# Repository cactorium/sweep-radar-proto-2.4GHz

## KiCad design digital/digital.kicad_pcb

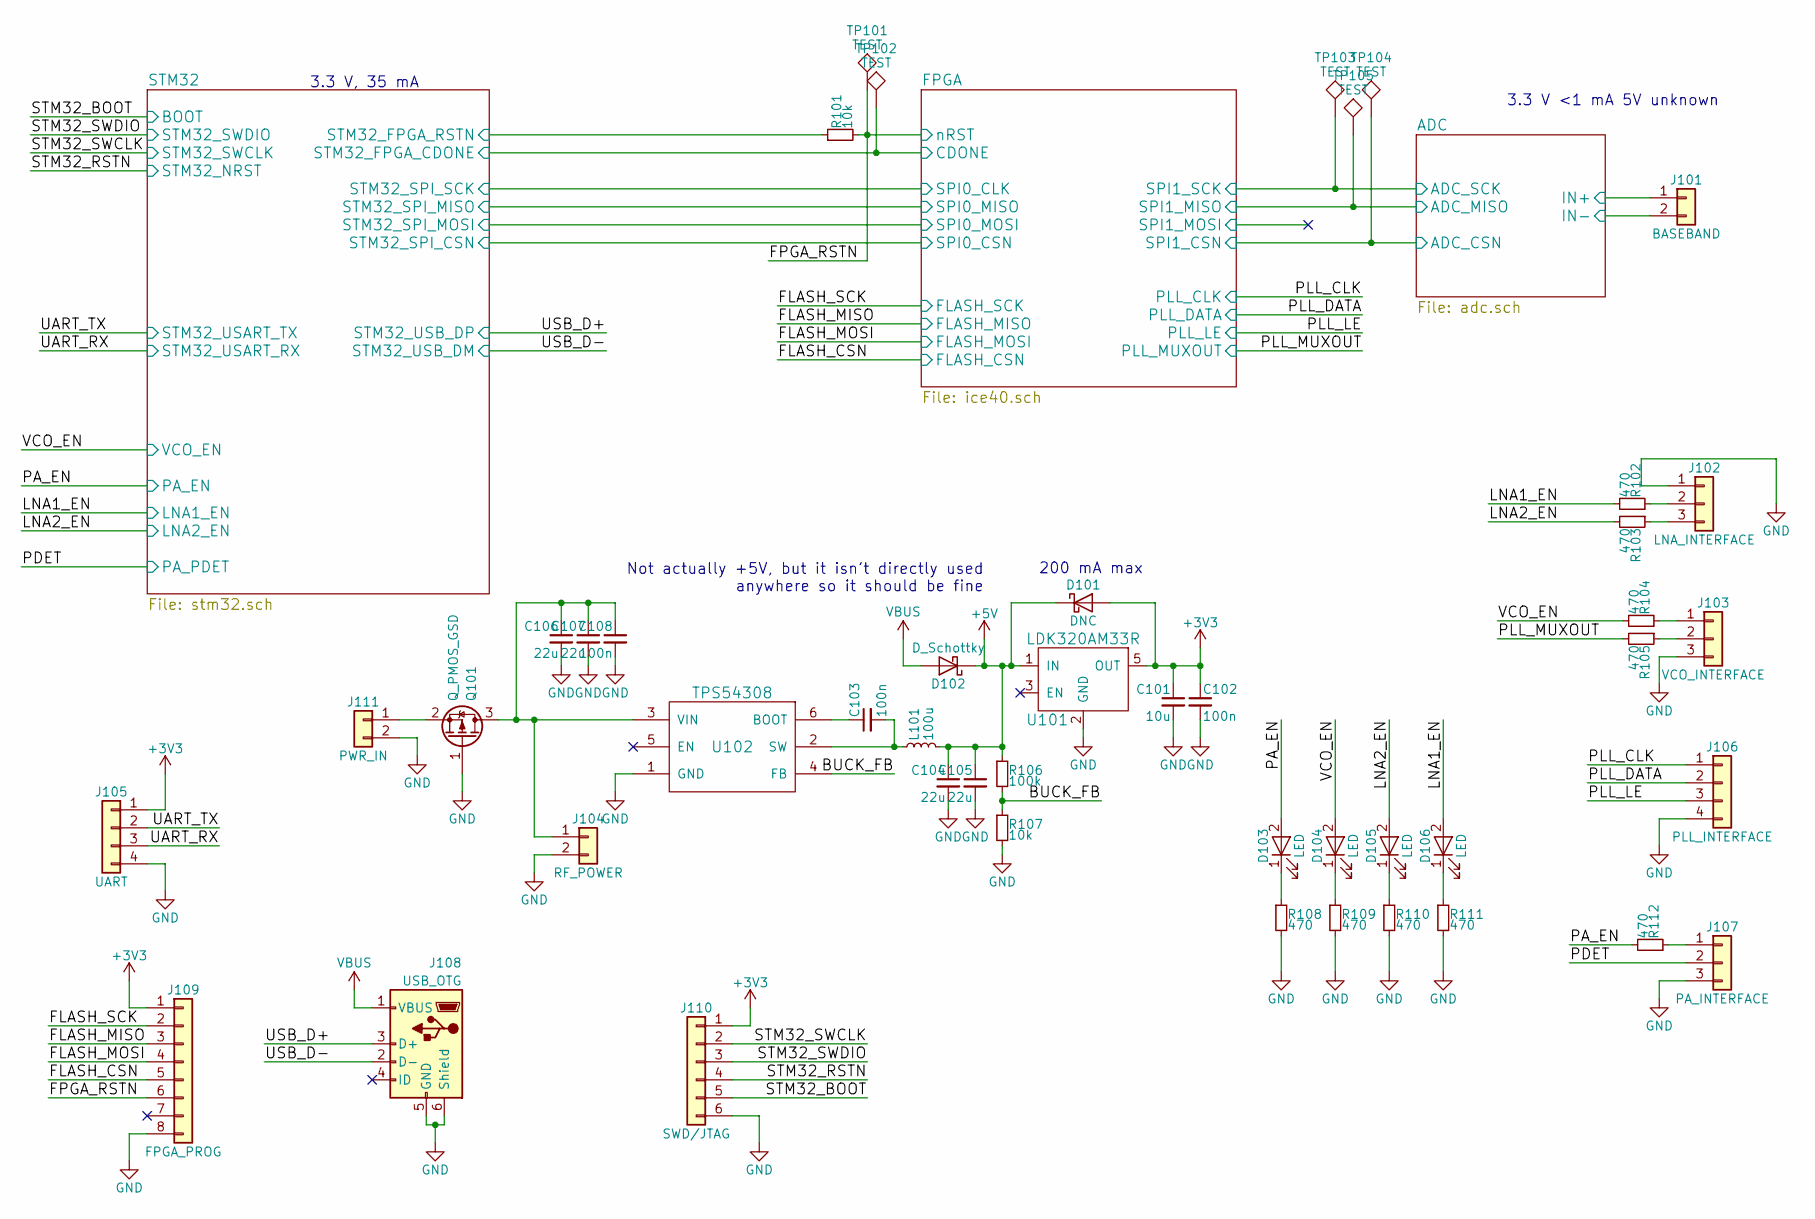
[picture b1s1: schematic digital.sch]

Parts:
C101: 10u; C_0805_HandSoldering
C102, C103, C108: 100n; C_0603_HandSoldering
C104, C105, C106, C107: 22u; C_1210_HandSoldering
D101: DNC; Panasonic_Diode-1006
D102: D_Schottky; Panasonic_Diode-1006
D103, D104, D105, D106: LED; D_0603
J101: BASEBAND; Pin_Header_Straight_1x02_Pitch2.54mm
J102: LNA_INTERFACE; Pin_Header_Straight_1x03_Pitch2.54mm
J103: VCO_INTERFACE; Pin_Header_Straight_1x03_Pitch2.54mm
J104: RF_POWER; Pin_Header_Straight_1x02_Pitch2.54mm
J105: UART; Pin_Header_Straight_2x02_Pitch2.54mm
J106: PLL_INTERFACE; Pin_Header_Straight_1x04_Pitch2.54mm
J107: PA_INTERFACE; Pin_Header_Straight_1x03_Pitch2.54mm
J108: USB_OTG; 10118194
J109: FPGA_PROG; Pin_Header_Straight_2x04_Pitch2.54mm
J110: SWD/JTAG; Pin_Header_Straight_2x03_Pitch2.54mm
J111: PWR_IN; Pin_Header_Straight_1x02_Pitch2.54mm
L101: 100u; Murata_DG6050C
Q101: Q_PMOS_GSD; SOT-23
R101, R107: 10k; R_0603_HandSoldering
R102, R103, R104, R105, R108, R109, R110, R111, R112: 470; R_0603_HandSoldering
R106: 100k; R_0402
TP101, TP102, TP103, TP104, TP105: TEST; 1Pin
U101: LDK320AM33R; ST_SOT23-5L
U102: TPS54308; TI-SOT-23-6

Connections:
+5V: C104.1, C105.1, D101.1 (K), D102.1 (K), L101.2, R106.1, U101.1 (IN); also elsewhere on the board
/ADC/ADC_CSN: TP104.1; also elsewhere on the board
/ADC/ADC_MISO: TP105.1; also elsewhere on the board
/ADC/ADC_SCK: TP103.1; also elsewhere on the board
/ADC/IN+: J101.1; also elsewhere on the board
/ADC/IN-: J101.2; also elsewhere on the board
/BUCK_FB: R106.2, R107.1, U102.4 (FB)
/FLASH_CSN: J109.3; also elsewhere on the board
/FLASH_MISO: J109.4; also elsewhere on the board
/FLASH_MOSI: J109.5; also elsewhere on the board
/FPGA/CDONE: TP102.1; also elsewhere on the board
/LNA1_EN: D106.2 (A), R102.2; also elsewhere on the board
/LNA2_EN: D105.2 (A), R103.2; also elsewhere on the board
/PA_EN: D103.2 (A), R112.2; also elsewhere on the board
/PDET: J107.2; also elsewhere on the board
/PLL_CLK: J106.1; also elsewhere on the board
/PLL_DATA: J106.2; also elsewhere on the board
/PLL_LE: J106.3; also elsewhere on the board
/PLL_MUXOUT: R105.2; also elsewhere on the board
/STM32/STM32_FPGA_RSTN: R101.1; also elsewhere on the board
/STM32_BOOT: J110.5; also elsewhere on the board
/STM32_RSTN: J110.4; also elsewhere on the board
/STM32_SWCLK: J110.2; also elsewhere on the board
/STM32_SWDIO: J110.3; also elsewhere on the board
/UART_RX: J105.3; also elsewhere on the board
/UART_TX: J105.2; also elsewhere on the board
/USB_D+: J108.3 (D+); also elsewhere on the board
/USB_D-: J108.2 (D-); also elsewhere on the board
/VCO_EN: D104.2 (A), R104.2; also elsewhere on the board
unnamed: C103.1, U102.6 (BOOT)
unnamed: C103.2, L101.1, U102.2 (SW)
unnamed: C106.1, C107.1, C108.1, J104.1, Q101.3 (D), U102.3 (VIN)
unnamed: D103.1 (K), R108.1
unnamed: D104.1 (K), R109.1
unnamed: D105.1 (K), R110.1
unnamed: D106.1 (K), R111.1
unnamed: J102.2, R102.1
unnamed: J102.3, R103.1
unnamed: J103.1, R104.1
unnamed: J103.2, R105.1
unnamed: J107.1, R112.1
unnamed: J111.1, Q101.2 (S)
VBUS: D102.2 (A), J108.1 (VBUS)

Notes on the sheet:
Not actually +5V, but it isn't directly used anywhere so it should be fine
200 mA max
3.3 V <1 mA 5V unknown
3.3 V, 35 mA

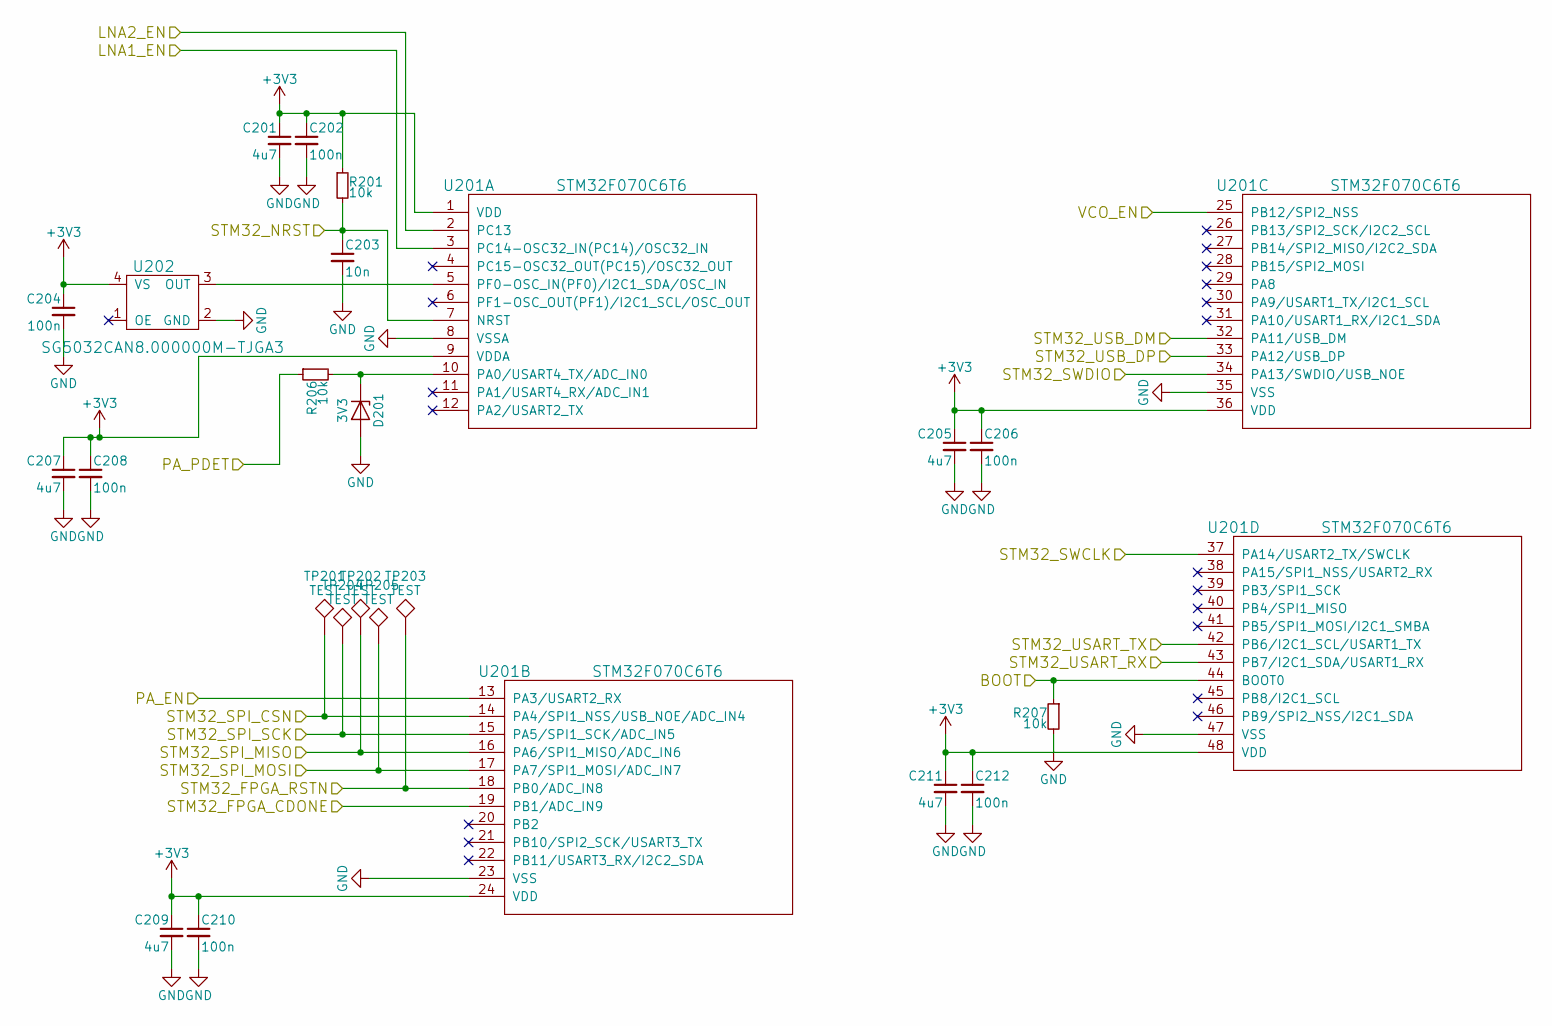
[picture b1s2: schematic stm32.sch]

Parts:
C201, C205, C207, C209, C211: 4u7; C_1206_HandSoldering
C202, C204, C206, C208, C210, C212: 100n; C_0603_HandSoldering
C203: 10n; C_0402
D201: 3V3; Diodes_SOD923
R201, R206, R207: 10k; R_0603_HandSoldering
TP201, TP202, TP203, TP204, TP205: TEST; Measurement_Point_Round-SMD-Pad_Small
U201: STM32F070C6T6; ST_LQFP48
U202: SG5032CAN8.000000M-TJGA3; Oscillator_SMD_SeikoEpson_SG8002LB-4pin_5.0x3.2mm_HandSolde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

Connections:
/FPGA/CDONE: U201.19 (PB1/ADC_IN9); also elsewhere on the board
/FPGA/SPI0_CLK: TP204.1, U201.15 (PA5/SPI1_SCK/ADC_IN5); also elsewhere on the board
/FPGA/SPI0_CSN: TP201.1, U201.14 (PA4/SPI1_NSS/USB_NOE/ADC_IN4); also elsewhere on the board
/FPGA/SPI0_MISO: TP202.1, U201.16 (PA6/SPI1_MISO/ADC_IN6); also elsewhere on the board
/FPGA/SPI0_MOSI: TP205.1, U201.17 (PA7/SPI1_MOSI/ADC_IN7); also elsewhere on the board
/LNA1_EN: U201.3 (PC14-OSC32_IN(PC14)/OSC32_IN); also elsewhere on the board
/LNA2_EN: U201.2 (PC13); also elsewhere on the board
/PA_EN: U201.13 (PA3/USART2_RX); also elsewhere on the board
/PDET: R206.1; also elsewhere on the board
/STM32/STM32_FPGA_RSTN: TP203.1, U201.18 (PB0/ADC_IN8); also elsewhere on the board
/STM32_BOOT: R207.1, U201.44 (BOOT0); also elsewhere on the board
/STM32_RSTN: C203.1, R201.2, U201.7 (NRST); also elsewhere on the board
/STM32_SWCLK: U201.37 (PA14/USART2_TX/SWCLK); also elsewhere on the board
/STM32_SWDIO: U201.34 (PA13/SWDIO/USB_NOE); also elsewhere on the board
/UART_RX: U201.43 (PB7/I2C1_SDA/USART1_RX); also elsewhere on the board
/UART_TX: U201.42 (PB6/I2C1_SCL/USART1_TX); also elsewhere on the board
/USB_D+: U201.33 (PA12/USB_DP); also elsewhere on the board
/USB_D-: U201.32 (PA11/USB_DM); also elsewhere on the board
/VCO_EN: U201.25 (PB12/SPI2_NSS); also elsewhere on the board
unnamed: D201.1 (K), R206.2, U201.10 (PA0/USART4_TX/ADC_IN0)
unnamed: U201.5 (PF0-OSC_IN(PF0)/I2C1_SDA/OSC_IN), U202.3 (OUT)

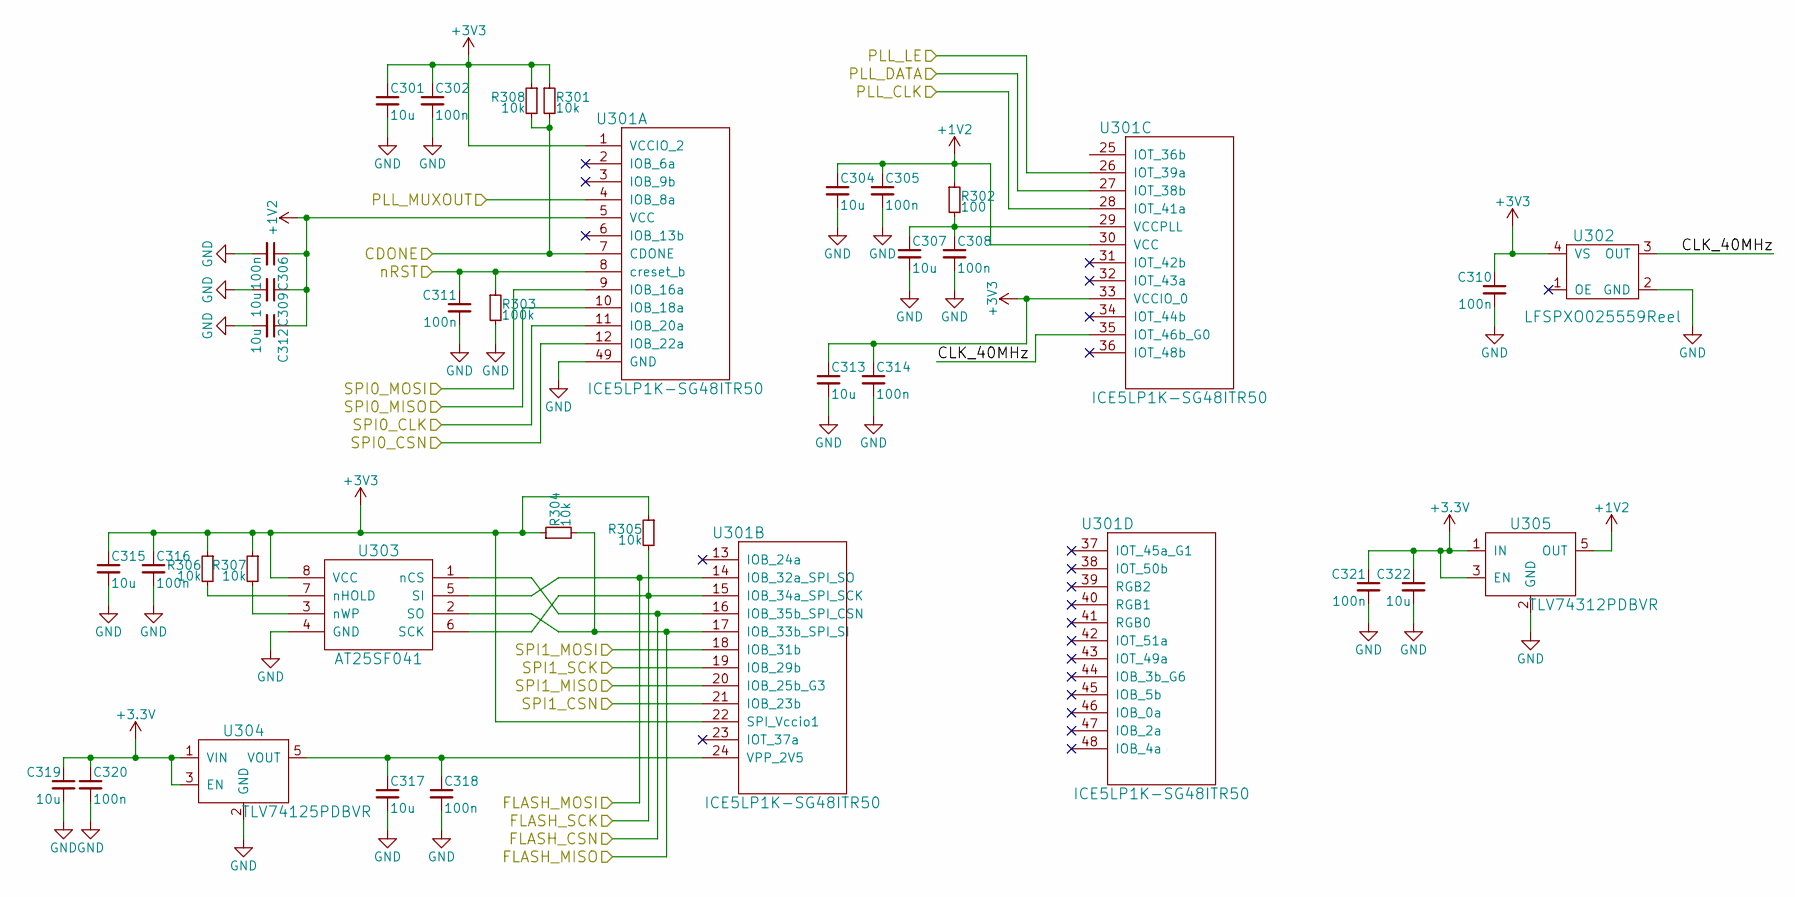
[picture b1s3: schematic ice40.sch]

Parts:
C301, C304, C307, C309, C312, C313, C315, C317, C319, C322: 10u; C_0805_HandSoldering
C302, C305, C306, C308, C310, C311, C314, C316, C318, C320, C321: 100n; C_0603_HandSoldering
R301, R304, R305, R306, R307, R308: 10k; R_0603_HandSoldering
R302: 100; R_0603_HandSoldering
R303: 100k; R_0402
U301: ICE5LP1K-SG48ITR50; Lattice_QFN48
U302: LFSPXO025559Reel; Crystal_SMD_3225-4pin_3.2x2.5mm_HandSoldering
U303: AT25SF041; SOIC-8_3.9x4.9mm_Pitch1.27mm
U304: TLV74125PDBVR; SOT-23-5_HandSoldering
U305: TLV74312PDBVR; SOT-23-5_HandSoldering

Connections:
+1V2: C304.1, C305.1, C306.1, C309.1, C312.1, R302.1, U301.5 (VCC), U301.30 (VCC), U305.5 (OUT)
/ADC/ADC_CSN: U301.21 (IOB_23b); also elsewhere on the board
/ADC/ADC_MISO: U301.20 (IOB_25b_G3); also elsewhere on the board
/ADC/ADC_SCK: U301.19 (IOB_29b); also elsewhere on the board
/FLASH_CSN: U301.16 (IOB_35b_SPI_CSN), U303.1 (nCS); also elsewhere on the board
/FLASH_MISO: R304.2, U301.17 (IOB_33b_SPI_SI), U303.2 (SO); also elsewhere on the board
/FLASH_MOSI: U301.14 (IOB_32a_SPI_SO), U303.5 (SI); also elsewhere on the board
/FPGA/CDONE: R301.2, R308.2, U301.7 (CDONE); also elsewhere on the board
/FPGA/CLK_40MHz: U301.35 (IOT_46b_G0), U302.3 (OUT)
/FPGA/SPI0_CLK: U301.11 (IOB_20a); also elsewhere on the board
/FPGA/SPI0_CSN: U301.12 (IOB_22a); also elsewhere on the board
/FPGA/SPI0_MISO: U301.10 (IOB_18a); also elsewhere on the board
/FPGA/SPI0_MOSI: U301.9 (IOB_16a); also elsewhere on the board
/PLL_CLK: U301.28 (IOT_41a); also elsewhere on the board
/PLL_DATA: U301.27 (IOT_38b); also elsewhere on the board
/PLL_LE: U301.26 (IOT_39a); also elsewhere on the board
/PLL_MUXOUT: U301.4 (IOB_8a); also elsewhere on the board
unnamed: C307.1, C308.1, R302.2, U301.29 (VCCPLL)
unnamed: C317.1, C318.1, U301.24 (VPP_2V5), U304.5 (VOUT)
unnamed: R306.2, U303.7 (nHOLD)
unnamed: R307.2, U303.3 (nWP)

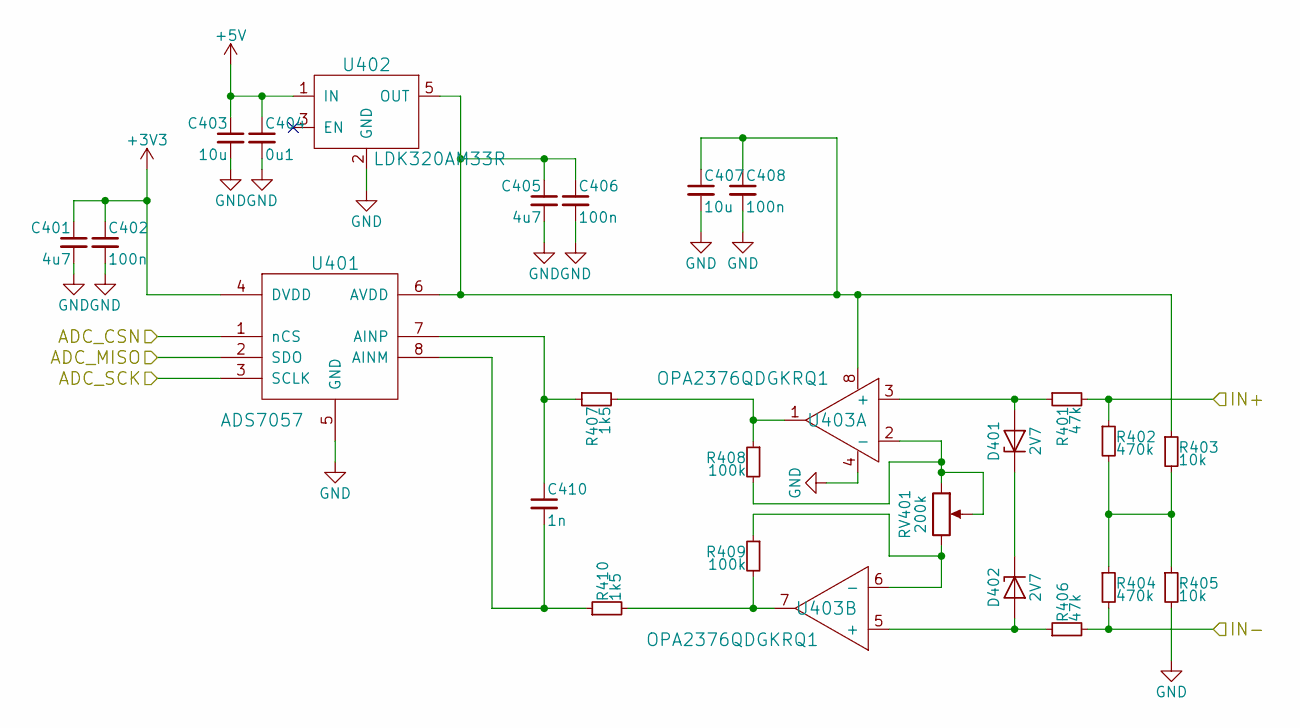
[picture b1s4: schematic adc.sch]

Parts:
C401, C405: 4u7; C_1206_HandSoldering
C402, C406, C408: 100n; C_0603_HandSoldering
C403, C407: 10u; C_0805_HandSoldering
C404: 0u1; C_0603_HandSoldering
C410: 1n; C_0603_HandSoldering
D401, D402: 2V7; D_SOD-323_HandSoldering
R401, R406: 47k; R_0603_HandSoldering
R402, R404: 470k; R_0402
R403, R405: 10k; R_0603_HandSoldering
R407, R410: 1k5; R_0402
R408, R409: 100k; R_0402
RV401: 200k; PT10LV10-204A2020
U401: ADS7057; TI_X2QFN8
U402: LDK320AM33R; ST_SOT23-5L
U403: OPA2376QDGKRQ1; TI_VSSOP8

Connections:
+5V: C403.1, C404.1, U402.1 (IN); also elsewhere on the board
/ADC/ADC_CSN: U401.1 (nCS); also elsewhere on the board
/ADC/ADC_MISO: U401.2 (SDO); also elsewhere on the board
/ADC/ADC_SCK: U401.3 (SCLK); also elsewhere on the board
/ADC/IN+: R401.2, R402.1; also elsewhere on the board
/ADC/IN-: R404.2, R406.2; also elsewhere on the board
unnamed: C405.1, C406.1, C407.1, C408.1, R403.1, U401.6 (AVDD), U402.5 (OUT), U403.8
unnamed: C410.1, R407.1, U401.7 (AINP)
unnamed: C410.2, R410.1, U401.8 (AINM)
unnamed: D401.1 (K), D402.1 (K)
unnamed: D401.2 (A), R401.1, U403.3 (+)
unnamed: D402.2 (A), R406.1, U403.5 (+)
unnamed: R402.2, R403.2, R404.1, R405.1
unnamed: R407.2, R408.1, U403.1
unnamed: R408.2, RV401.1, RV401.2, U403.2 (-)
unnamed: R409.1, RV401.3, U403.6 (-)
unnamed: R409.2, R410.2, U403.7

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
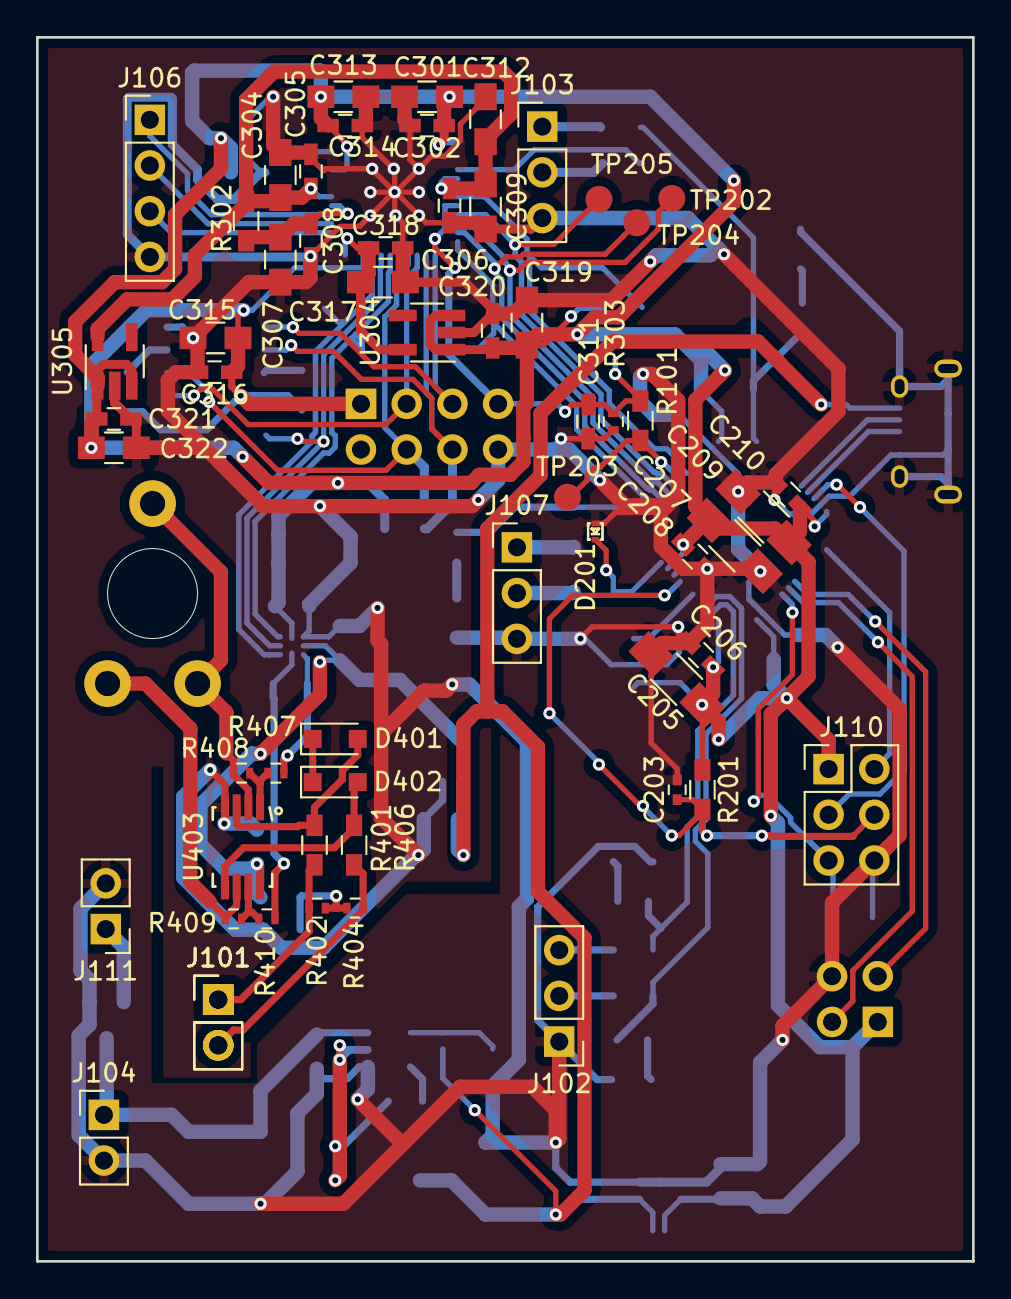
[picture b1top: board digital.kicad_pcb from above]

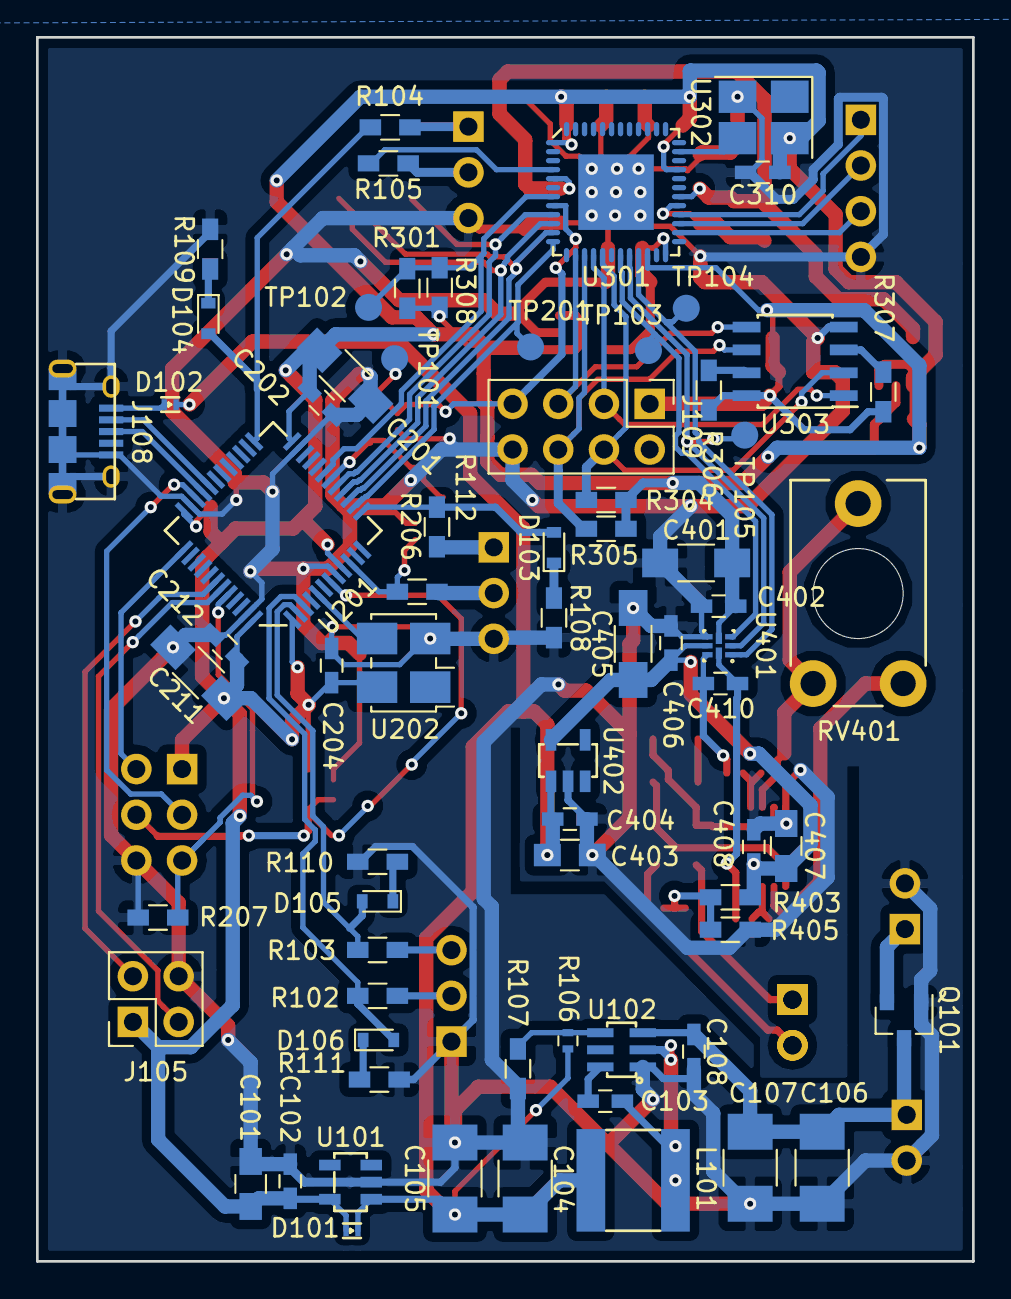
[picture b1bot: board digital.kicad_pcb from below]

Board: 2 copper layers, 52.0 x 68.0 mm, 129 parts (71 on the bottom side), 70 nets.

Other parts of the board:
J101#2: BASEBAND; Pin_Header_Straight_1x02_Pitch2.54mm

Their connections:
/ADC/IN+: J101#2.1; also elsewhere on the board
/ADC/IN-: J101#2.2; also elsewhere on the board

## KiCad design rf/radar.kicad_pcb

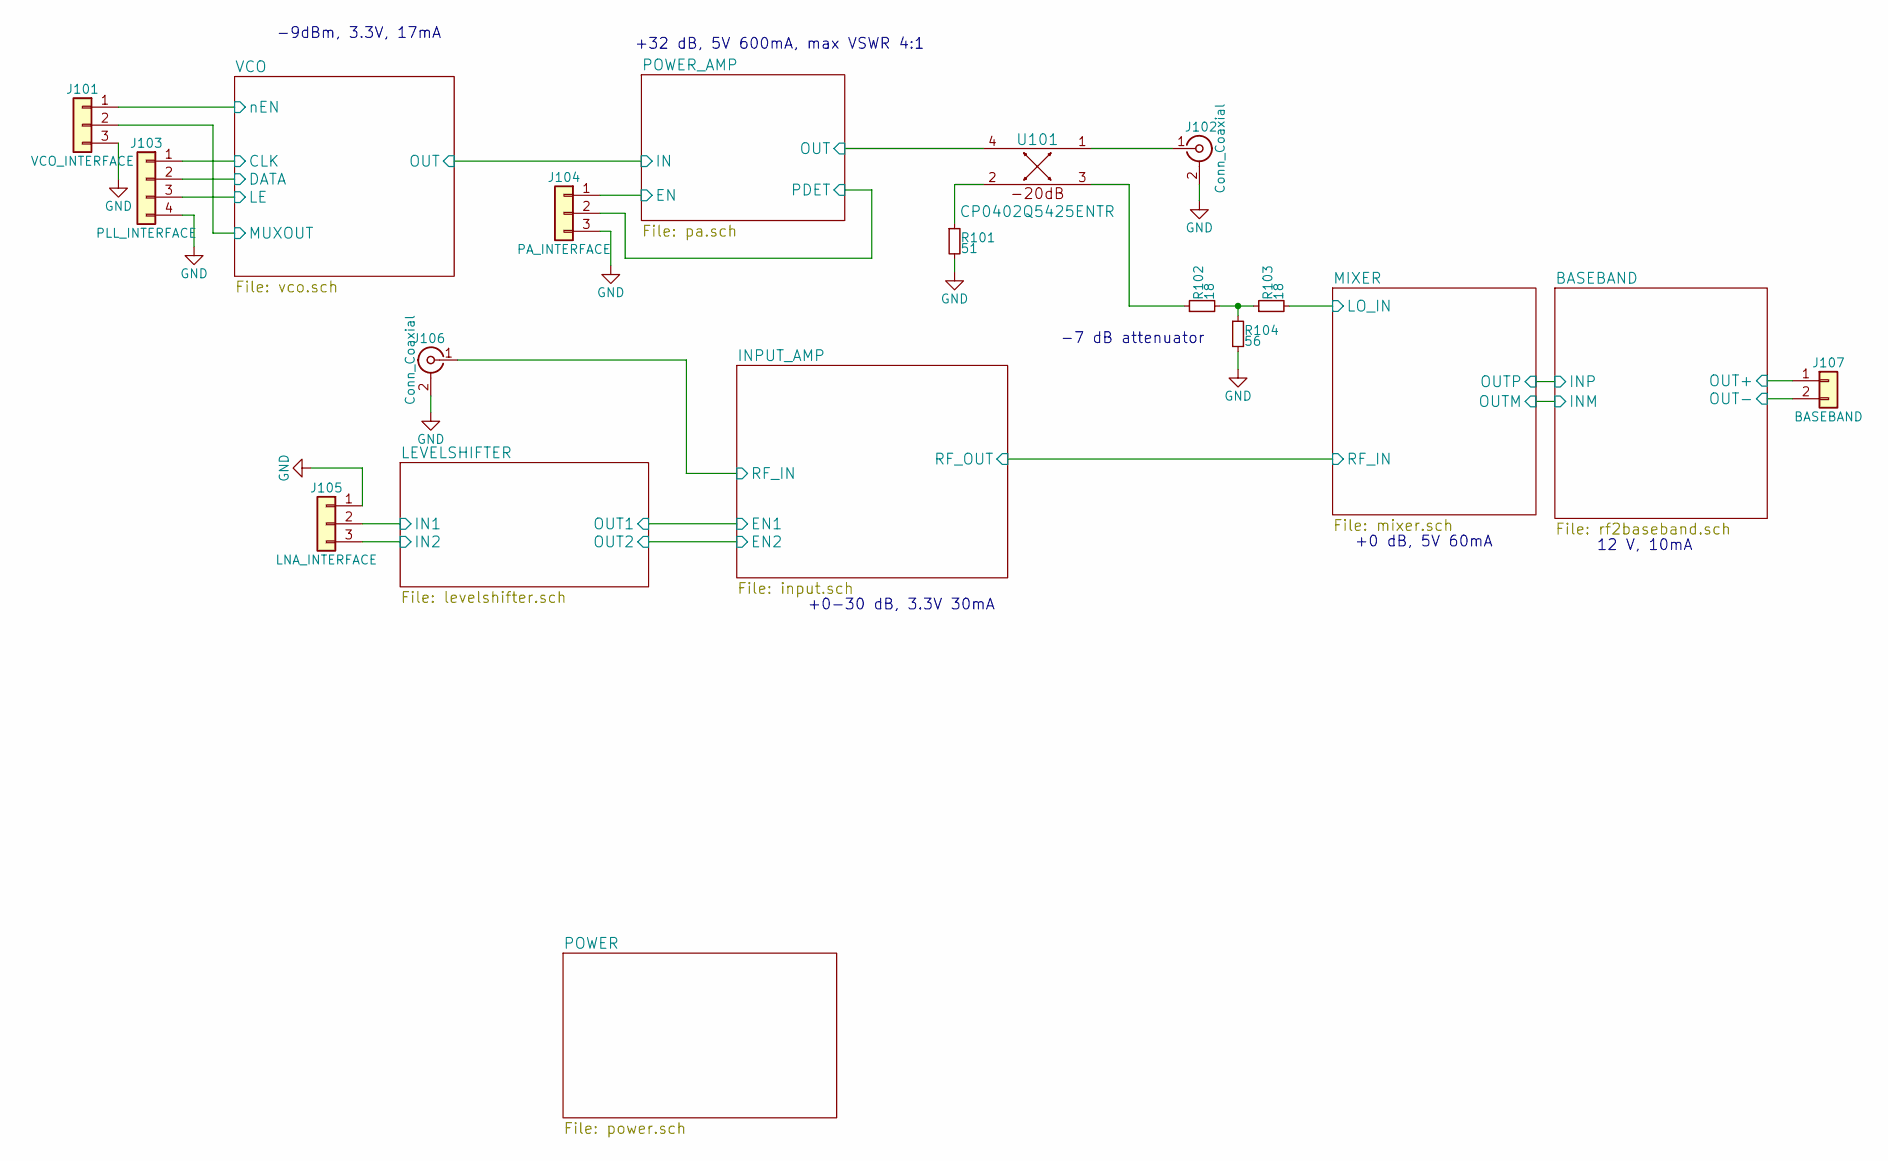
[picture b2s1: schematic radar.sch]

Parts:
J101: VCO_INTERFACE; Socket_Strip_Straight_1x03_Pitch2.54mm
J102, J106: Conn_Coaxial; 132322
J103: PLL_INTERFACE; Socket_Strip_Straight_1x04_Pitch2.54mm
J104: PA_INTERFACE; Socket_Strip_Straight_1x03_Pitch2.54mm
J105: LNA_INTERFACE; Socket_Strip_Straight_1x03_Pitch2.54mm
J107: BASEBAND; Pin_Header_Straight_1x02_Pitch2.54mm
R101: 51; R_0402
R102, R103: 18; R_0402
R104: 56; R_0402
U101: CP0402Q5425ENTR; CP0402

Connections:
/BASEBAND/OUT+: J107.1; also elsewhere on the board
/BASEBAND/OUT-: J107.2; also elsewhere on the board
/INPUT_AMP/RF_IN: J106.1 (In); also elsewhere on the board
/LEVELSHIFTER/IN1: J105.2; also elsewhere on the board
/LEVELSHIFTER/IN2: J105.3; also elsewhere on the board
/MIXER/LO_IN: R103.2; also elsewhere on the board
/POWER_AMP/EN: J104.1; also elsewhere on the board
/POWER_AMP/OUT: U101.4; also elsewhere on the board
/POWER_AMP/PDET: J104.2; also elsewhere on the board
/VCO/CLK: J103.1; also elsewhere on the board
/VCO/DATA: J103.2; also elsewhere on the board
/VCO/LE: J103.3; also elsewhere on the board
/VCO/MUXOUT: J101.2; also elsewhere on the board
/VCO/nEN: J101.1; also elsewhere on the board
GND: J101.3, J102.2 (Ext), J103.4, J104.3, J105.1, J106.2 (Ext), R101.2, R104.2; also elsewhere on the board
unnamed: J102.1 (In), U101.1
unnamed: R101.1, U101.2
unnamed: R102.1, U101.3
unnamed: R102.2, R103.1, R104.1

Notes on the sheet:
-9dBm, 3.3V, 17mA
+32 dB, 5V 600mA, max VSWR 4:1
+0 dB, 5V 60mA
+0-30 dB, 3.3V 30mA
12 V, 10mA
-7 dB attenuator

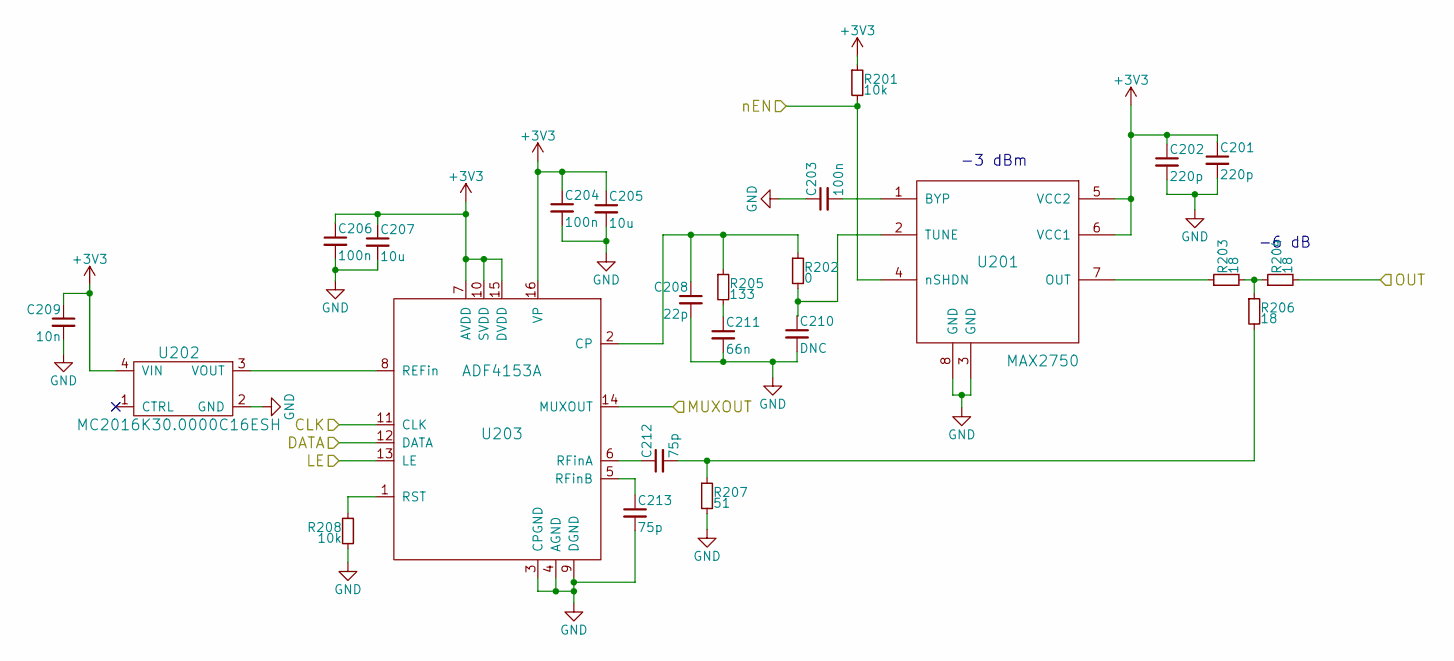
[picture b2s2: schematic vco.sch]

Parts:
C201, C202: 220p; C_0402
C203, C204, C206: 100n; C_0603_HandSoldering
C205, C207: 10u; C_0805_HandSoldering
C208: 22p; C_0603_HandSoldering
C209: 10n; C_0402
C210: DNC; C_0603_HandSoldering
C211: 66n; C_0805_HandSoldering
C212, C213: 75p; C_0402
R201, R208: 10k; R_0603_HandSoldering
R202: 0; R_0603_HandSoldering
R203, R204: 18; R_0402
R205: 133; R_0805_HandSoldering
R206: 18; C_0402
R207: 51; R_0402
U201: MAX2750; U8+1
U202: MC2016K30.0000C16ESH
U203: ADF4153A; TSSOP-16

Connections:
+3V3: C201.1, C202.1, C204.1, C205.1, C206.1, C207.1, C209.1, R201.1, U201.5 (VCC2), U201.6 (VCC1), U202.4 (VIN), U203.7 (AVDD), U203.10 (SVDD), U203.15 (DVDD), U203.16 (VP); also elsewhere on the board
/POWER_AMP/IN: R204.2; also elsewhere on the board
/VCO/CLK: U203.11 (CLK); also elsewhere on the board
/VCO/DATA: U203.12 (DATA); also elsewhere on the board
/VCO/LE: U203.13 (LE); also elsewhere on the board
/VCO/MUXOUT: U203.14 (MUXOUT); also elsewhere on the board
/VCO/nEN: R201.2, U201.4 (nSHDN); also elsewhere on the board
GND: C201.2, C202.2, C203.1, C204.2, C205.2, C206.2, C207.2, C208.2, C209.2, C210.2, C211.2, C213.2, R207.2, R208.2, U201.3 (GND), U201.8 (GND), U202.2 (GND), U203.3 (CPGND), U203.4 (AGND), U203.9 (DGND); also elsewhere on the board
unnamed: C203.2, U201.1 (BYP)
unnamed: C208.1, R202.1, R205.1, U203.2 (CP)
unnamed: C210.1, R202.2, U201.2 (TUNE)
unnamed: C211.1, R205.2
unnamed: C212.1, U203.6 (RFinA)
unnamed: C212.2, R206.2, R207.1
unnamed: C213.1, U203.5 (RFinB)
unnamed: R203.1, U201.7 (OUT)
unnamed: R203.2, R204.1, R206.1
unnamed: R208.1, U203.1 (RST)
unnamed: U202.3 (VOUT), U203.8 (REFin)

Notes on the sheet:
-6 dB
-3 dBm

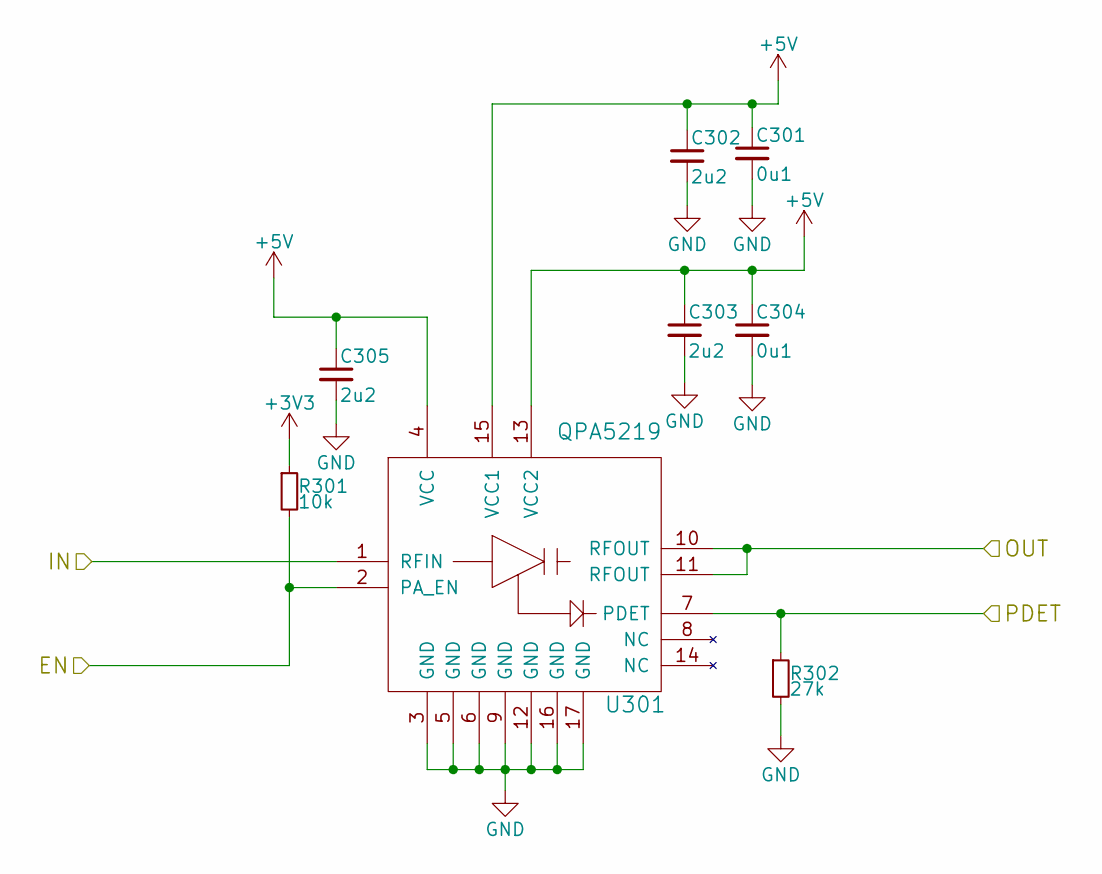
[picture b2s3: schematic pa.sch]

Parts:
C301, C304: 0u1; C_0603_HandSoldering
C302, C303, C305: 2u2; C_0805_HandSoldering
R301: 10k; R_0603_HandSoldering
R302: 27k; R_0603_HandSoldering
U301: QPA5219

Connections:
+3V3: R301.1; also elsewhere on the board
+5V: C301.1, C302.1, C303.1, C304.1, C305.1, U301.4 (VCC), U301.13 (VCC2), U301.15 (VCC1); also elsewhere on the board
/POWER_AMP/EN: R301.2, U301.2 (PA_EN); also elsewhere on the board
/POWER_AMP/IN: U301.1 (RFIN); also elsewhere on the board
/POWER_AMP/OUT: U301.10 (RFOUT), U301.11 (RFOUT); also elsewhere on the board
/POWER_AMP/PDET: R302.1, U301.7 (PDET); also elsewhere on the board
GND: C301.2, C302.2, C303.2, C304.2, C305.2, R302.2, U301.3 (GND), U301.5 (GND), U301.6 (GND), U301.9 (GND), U301.12 (GND), U301.16 (GND), U301.17 (GND); also elsewhere on the board

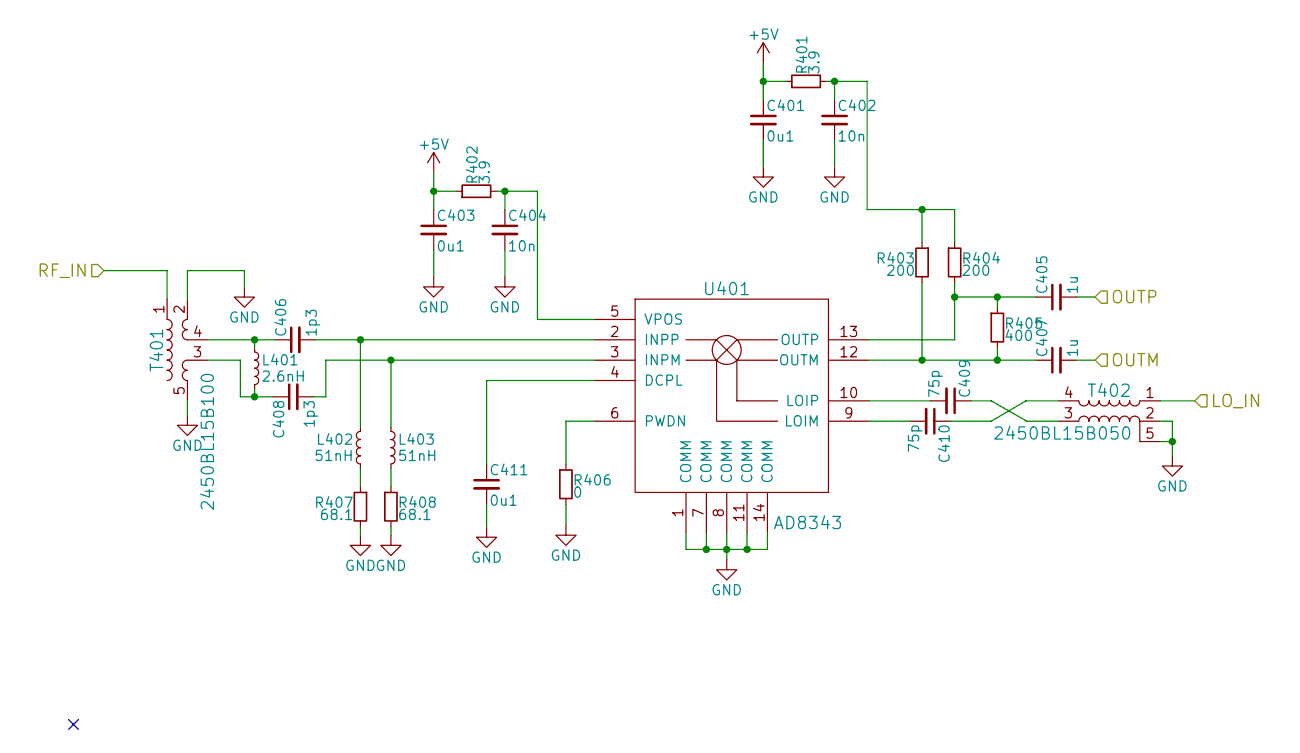
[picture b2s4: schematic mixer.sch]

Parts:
C401, C403, C411: 0u1; C_0603_HandSoldering
C402, C404: 10n; C_0402
C405, C407: 1u; C_0603_HandSoldering
C406, C408: 1p3; C_0201
C409, C410: 75p; C_0402
L401: 2.6nH; C_0201
L402, L403: 51nH; C_0402
R401, R402: 3.9; R_0603_HandSoldering
R403, R404: 200; R_1206_HandSoldering
R405: 400; R_1206_HandSoldering
R406: 0; R_0603_HandSoldering
R407, R408: 68.1; R_1206_HandSoldering
T401: 2450BL15B100
T402: 2450BL15B050; 2450BL15B100
U401: AD8343; TSSOP-14_4.4x5mm_Pitch0.65mm

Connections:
+5V: C401.1, C403.1, R401.1, R402.1; also elsewhere on the board
/BASEBAND/INM: C407.2; also elsewhere on the board
/BASEBAND/INP: C405.2; also elsewhere on the board
/MIXER/LO_IN: T402.1; also elsewhere on the board
/MIXER/RF_IN: T401.1; also elsewhere on the board
GND: C401.2, C402.2, C403.2, C404.2, C411.2, R406.2, R407.2, R408.2, T401.2, T401.5, T402.2, T402.5, U401.1 (COMM), U401.7 (COMM), U401.8 (COMM), U401.11 (COMM), U401.14 (COMM); also elsewhere on the board
unnamed: C402.1, R401.2, R403.1, R404.1
unnamed: C404.1, R402.2, U401.5 (VPOS)
unnamed: C405.1, R404.2, R405.1, U401.13 (OUTP)
unnamed: C406.1, L401.1, T401.4
unnamed: C406.2, L402.1, U401.2 (INPP)
unnamed: C407.1, R403.2, R405.2, U401.12 (OUTM)
unnamed: C408.1, L401.2, T401.3
unnamed: C408.2, L403.1, U401.3 (INPM)
unnamed: C409.1, T402.3
unnamed: C409.2, U401.10 (LOIP)
unnamed: C410.1, T402.4
unnamed: C410.2, U401.9 (LOIM)
unnamed: C411.1, U401.4 (DCPL)
unnamed: L402.2, R407.1
unnamed: L403.2, R408.1
unnamed: R406.1, U401.6 (PWDN)
